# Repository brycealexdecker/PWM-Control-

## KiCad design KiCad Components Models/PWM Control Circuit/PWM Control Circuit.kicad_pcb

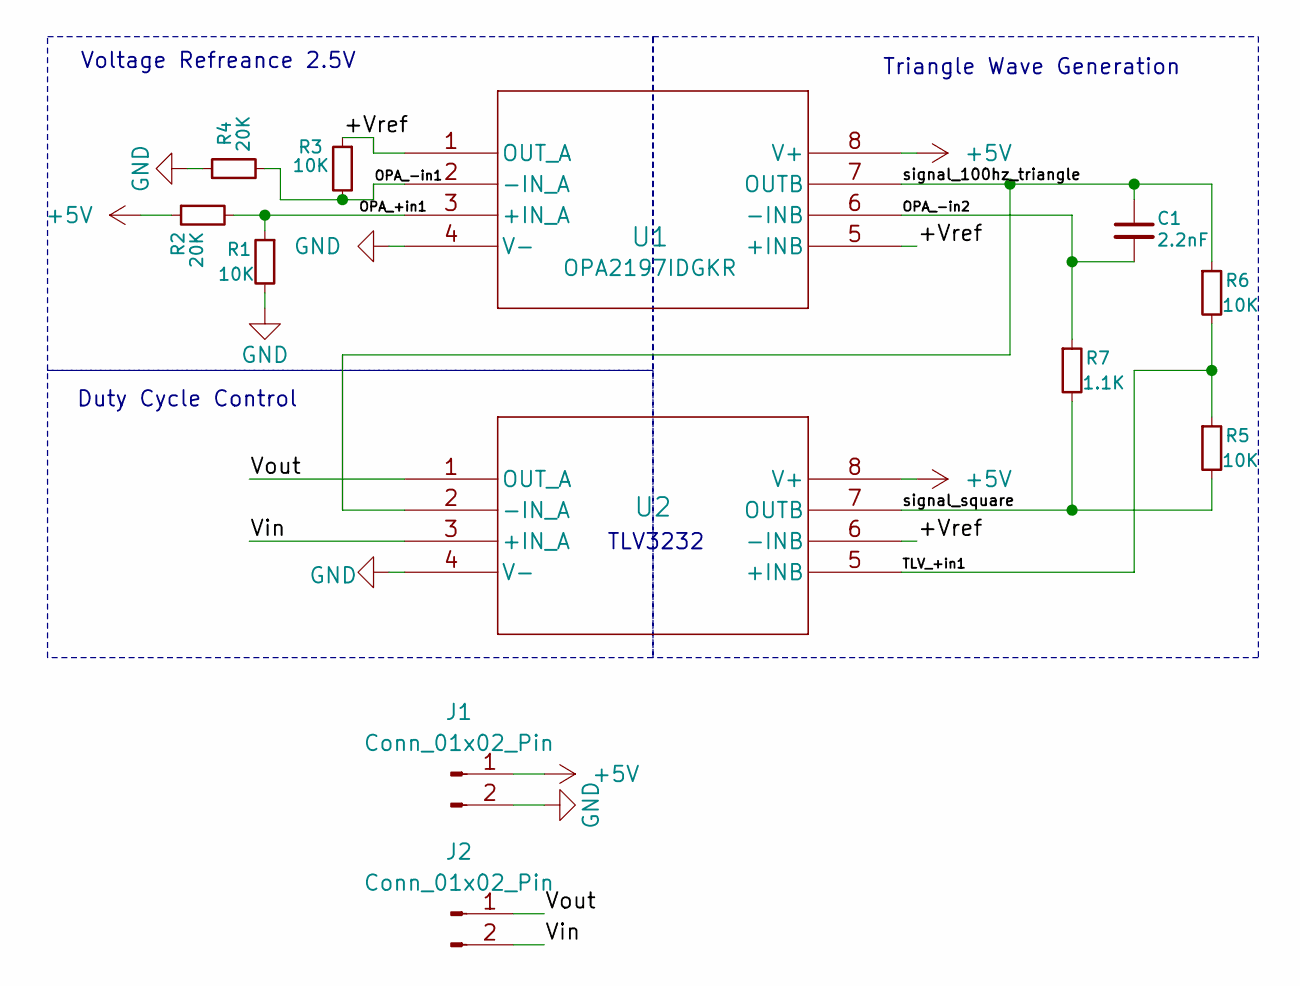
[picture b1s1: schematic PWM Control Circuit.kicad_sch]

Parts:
C1: 2.2nF; C_0201_0603Metric_Pad0.64x0.40mm_HandSolder
J1, J2: Conn_01x02_Pin; PinHeader_1x02_P1.00mm_Vertical_SMD_Pin1Left
R1, R3, R5, R6: 10K; R_Axial_DIN0204_L3.6mm_D1.6mm_P5.08mm_Horizontal
R2, R4: 20K; R_Axial_DIN0204_L3.6mm_D1.6mm_P5.08mm_Horizontal
R7: 1.1K; R_Axial_DIN0204_L3.6mm_D1.6mm_P5.08mm_Horizontal
U1, U2: OPA2197IDGKR; DGK8_TEX

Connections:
+5V: J1.1, R2.1, U1.8 (V+), U2.8 (V+)
/+Vref: R3.1, U1.1 (OUT_A), U1.5 (+INB), U2.6 (-INB)
/OPA_+in1: R1.1, R2.2, U1.3 (+IN_A)
/OPA_-in1: R3.2, R4.2, U1.2 (-IN_A)
/OPA_-in2: C1.2, R7.1, U1.6 (-INB)
/TLV_+in1: R5.1, R6.2, U2.5 (+INB)
/Vin: J2.2, U2.3 (+IN_A)
/Vout: J2.1, U2.1 (OUT_A)
/signal_100hz_triangle: C1.1, R6.1, U1.7 (OUTB), U2.2 (-IN_A)
/signal_square: R5.2, R7.2, U2.7 (OUTB)
GND: J1.2, R1.2, R4.1, U1.4 (V-), U2.4 (V-)

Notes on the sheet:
Voltage Refreance 2.5V
Triangle Wave Generation
Duty Cycle Control
TLV3232

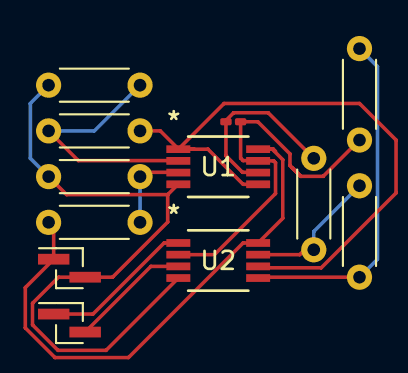
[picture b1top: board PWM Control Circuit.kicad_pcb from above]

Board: 2 copper layers, 12 parts (0 on the bottom side), 11 nets.

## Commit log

2025-12-27 PDF of Insperation
2025-12-27 inspo
2025-12-28 TLV3231 Spice and Datasheet
2025-12-28 Working Spice Modle
2026-01-02 PCB design done
